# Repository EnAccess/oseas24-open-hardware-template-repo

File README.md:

<p align="center">
  
</p>
<p align="center">
    9-10 May | Open Source in Energy Access Symposium Hackathon
</p>

---

## Open Hardware Template Repository

**Stack:** KiCAD, Python scripting

**Helpful experiences:** KiCAD automation, CI/CD pipelines

**Abstract:** The tooling for Open Hardware repositories is currently undergoing rapid development. It can be overwhelming for an electrical engineer working on the PCB’s to follow up on all this.

## Challenge

The goal of this workgroup is to create a KiCAD template repository with the some of following features (in no particular order)

- Automatic diff generation for PCB’s and Schematics
- KiCanvas WebViewer Link integration
- CI pipeline to run lint checks: DRC rules check, conventions, etc..
- Release management, using GitHub tags
- Workflow to update the release tag as labels on the PCB
- Deploy workflow that generates production files and makes them available in the release (not part of version control)
- Auto-generated documentation (incl. versioning)
- Deployment of documentation (keeping docs of older PCB revisions)

This repo uses a sample KiCAD PCB from the [Cicada Project](https://github.com/EnAccess/Cicada-GSM-HW).

As part of the Open BMS we have already explored some features of the amazing KiBot tool. Also, the recent release of KiCAD v8 enriches the native KiCAD CLI with some features

**Expected outcome:** The optimal outcome of this challenge would be a repository template including all above mentioned features and integrations. However we know time is short and anything getting us closer to this can be a great success (e.g. an early draft repo + a detailed specifications and to-do list).

## Getting Started

- Join the OSEAS24 Discord server: https://community.oseas.org/
- Introduce yourself in #introductions channel and join this topic’s channel
- Confirm you have access to the following Repos
  - https://github.com/EnAccess/oseas24-open-hardware-template-repo
- For physical participants: Bring a computer (and required Adapters) for some hacking 🤖🧑‍💻
- Read through the information and resources section

Contact person(s): Daniel (remote) / Martin (remote)

## Further information and resources

- https://github.com/LibreSolar/bms-c1/pull/48
- https://www.kicad.org/blog/2024/02/Version-8.0.0-Released/
- https://github.com/INTI-CMNB/KiBot
- KiCanvas: KiCad web viewer
  - Link: https://kicanvas.org/
  - Example: https://kicanvas.org/?github=https%3A%2F%2Fgithub.com%2FLibreSolar%2Fbms-c1%2Ftree%2Fmain%2Fkicad
- Interactive HTML BoM
  - https://github.com/openscopeproject/InteractiveHtmlBom
- Other example of nice project: https://github.com/OpenCleanEnergy/OpenMI

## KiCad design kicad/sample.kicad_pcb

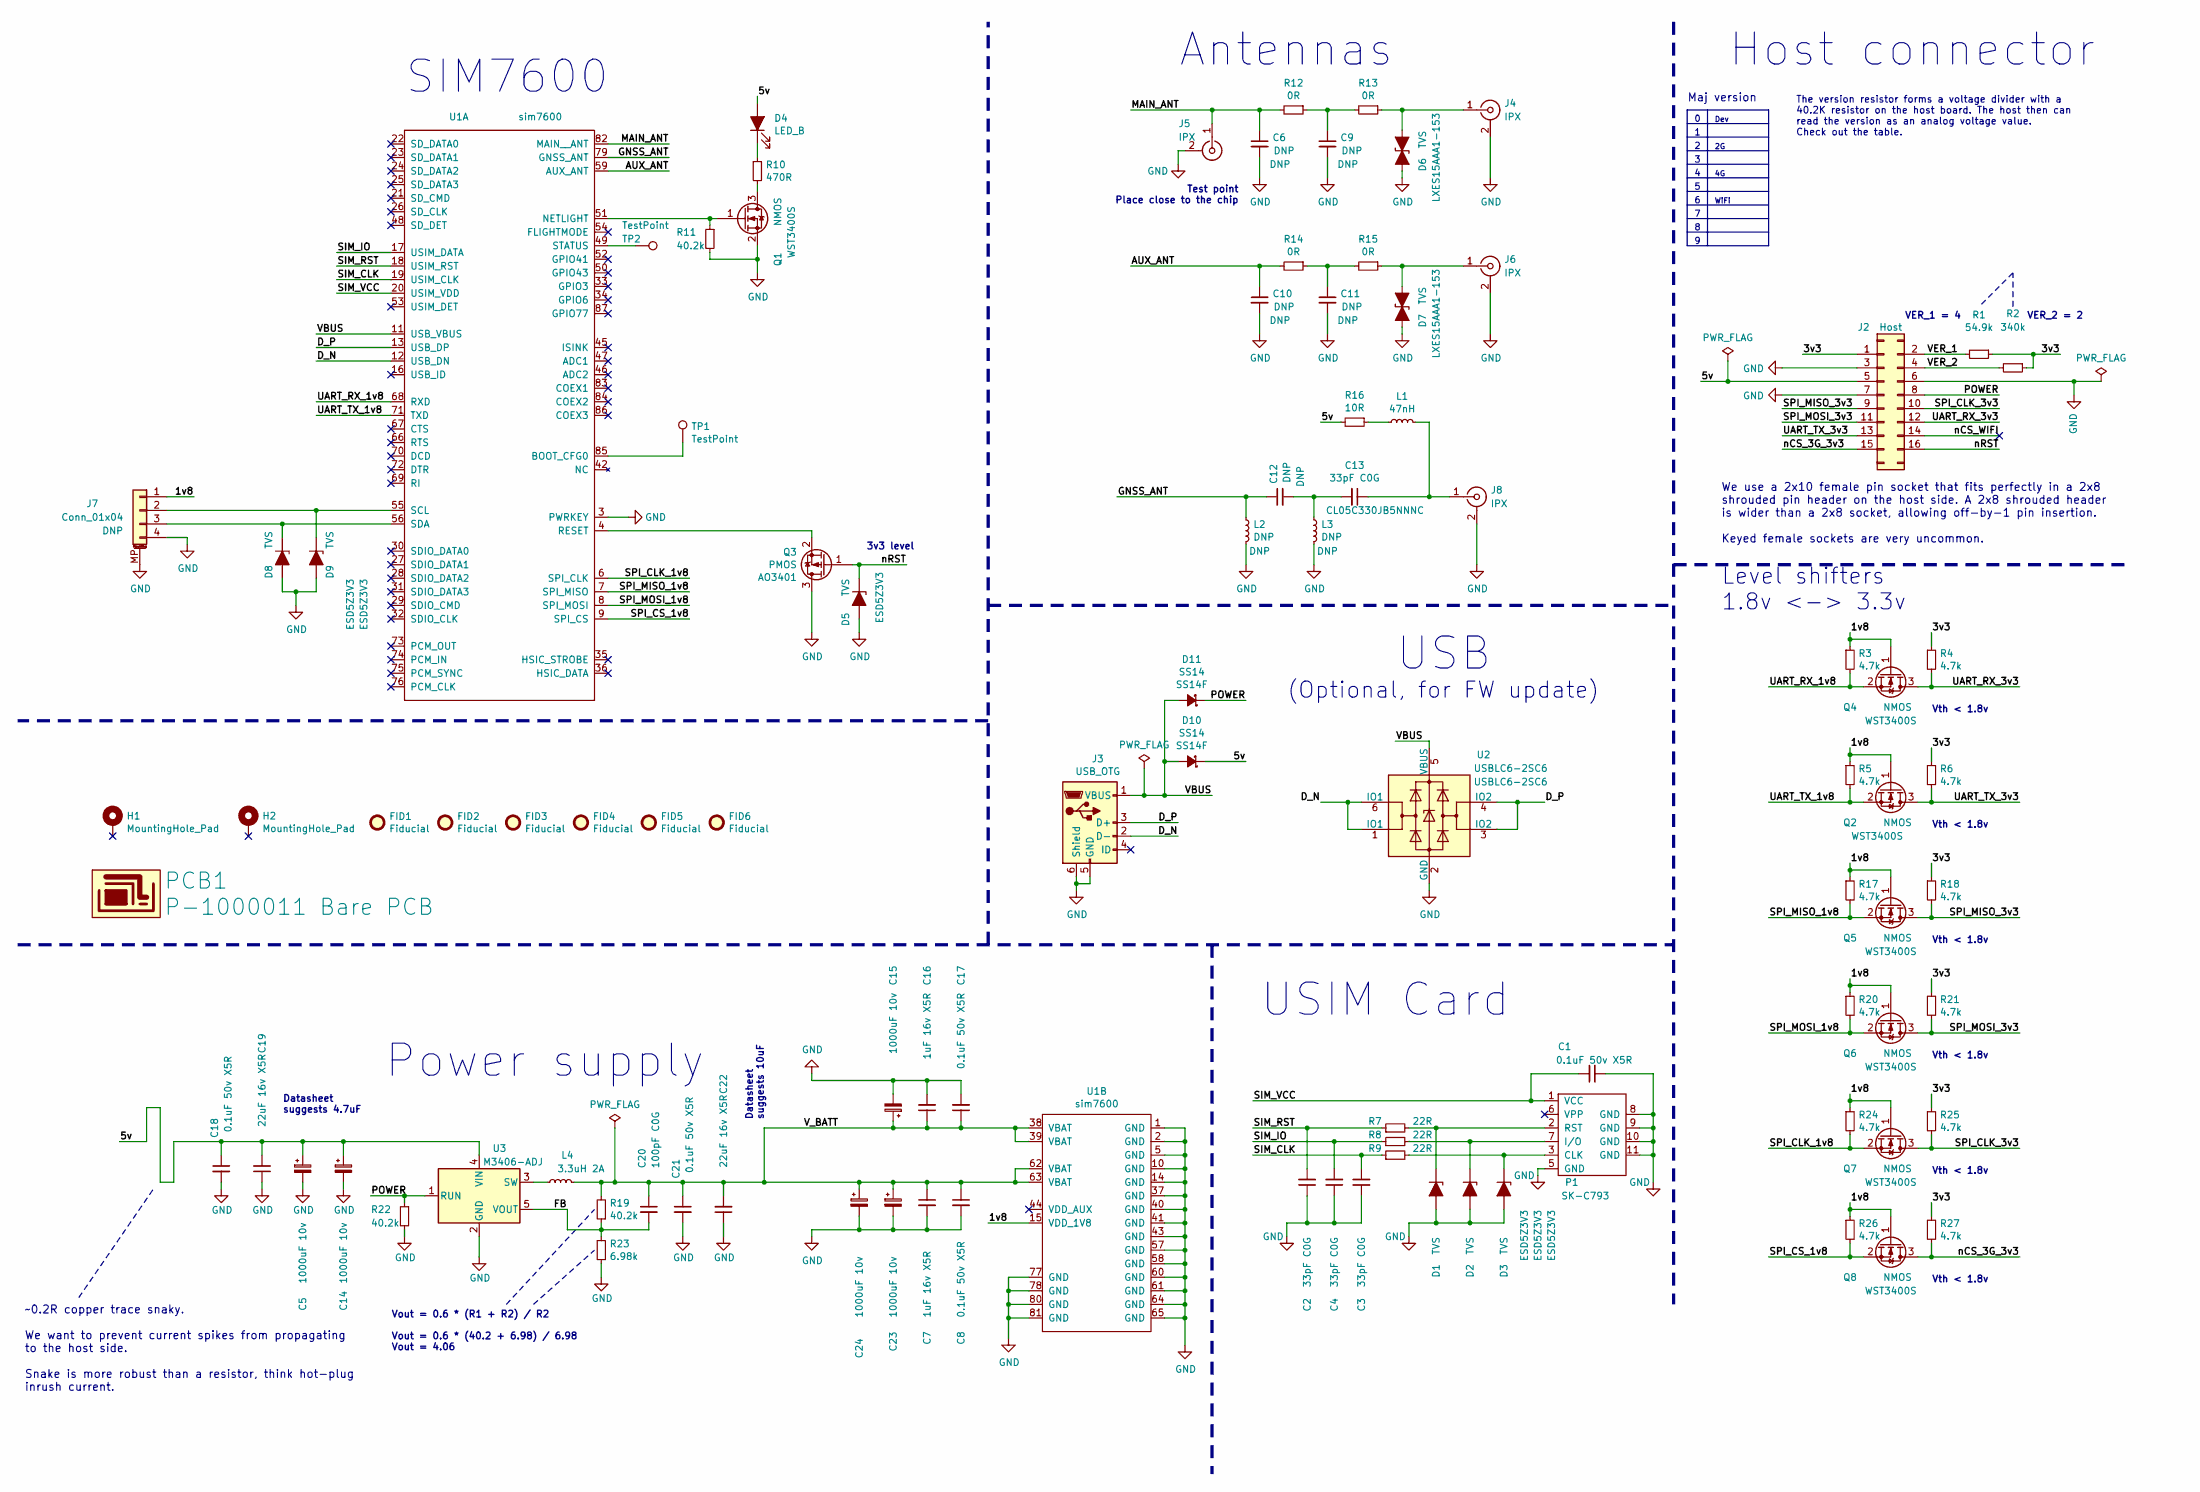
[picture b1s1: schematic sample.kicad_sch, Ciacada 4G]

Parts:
C1, C8, C17, C18, C21: 0.1uF 50v X5R; C_0603_1608Metric; MPN CL10B104KB8NNNC
C2, C3, C4, C13: 33pF C0G; C_0402_1005Metric; MPN CL05C330JB5NNNC
C5, C14, C15, C23, C24: 1000uF 10v; CP_Radial_D8.0mm_P3.50mm; MPN C3299
C6, C9, C10, C11, C12: DNP; C_0402_1005Metric
C7, C16: 1uF 16v X5R; C_0603_1608Metric; MPN CL10A105KB8NNNC
C19, C22: 22uF 16v X5R; C_0805_2012Metric; MPN CL21A226MOQNNNE
C20: 100pF C0G; C_0402_1005Metric; MPN CL05C101JB5NNNC
D1, D2, D3, D5, D8, D9: TVS; D_SOD-523; MPN ESD5Z3V3
D4: LED_B; D_0603_1608Metric; MPN BL-HB336G-TRB
D6, D7: TVS; D_0402_1005Metric; MPN LXES15AAA1-153
D10, D11: SS14; D_SMA; MPN SS14F
FID1, FID2, FID3, FID4, FID5, FID6: Fiducial; Fiducial_1mm_Mask2mm
H1, H2: MountingHole_Pad; MountingHole_3.2mm_M3_ISO14580_Pad
J2: Host; PinSocket_2x08_P2.54mm_Vertical_padded; MPN C30867
J3: USB_OTG; ZX62D-B-5PA8; MPN C10418
J4, J5, J6, J8: IPX; U.FL_Molex_MCRF_73412-0110_Vertical; MPN U.FL-R-SMT-1(80)
J7: Conn_01x04; JST_PH_S4B-PH-SM4-TB_1x04-1MP_P2.00mm_Horizontal
L1: 47nH; L_0402_1005Metric; MPN SDCL1005C47NJTDF
L2, L3: DNP; L_0402_1005Metric
L4: 3.3uH 2A; L_4030_Handsoldering; MPN FPI0403F-3R3M
P1: SK-C793; MPN SK-C793
PCB1: P-1000011 Bare PCB
Q1, Q2, Q4, Q5, Q6, Q7, Q8: NMOS; SOT-23; MPN WST3400S
Q3: PMOS; SOT-23; MPN AO3401
R1: 54.9k; R_0402_1005Metric; MPN 0402WGF5492TCE
R2: 340k; R_0402_1005Metric; MPN 0402WGF3403TCE
R3, R4, R5, R6, R17, R18, R20, R21, R24, R25, R26, R27: 4.7k; R_0402_1005Metric; MPN 0402WGF4701TCE
R7, R8, R9: 22R; R_0402_1005Metric; MPN 0402WGF220JTCE
R10: 470R; R_0402_1005Metric; MPN 0402WGF4700TCE
R11, R19, R22: 40.2k; R_0402_1005Metric; MPN 0402WGF4022TCE
R12, R13, R14, R15: 0R; R_0402_1005Metric; MPN 0402WGF0000TCE
R16: 10R; R_0402_1005Metric; MPN 0402WGF100JTCE
R23: 6.98k; R_0402_1005Metric; MPN 0402WGF6981TCE
TP1, TP2: TestPoint; TestPoint_Pad_D1.5mm
U1: sim7600; MPN SIM7600CE-L1C
U2: USBLC6-2SC6; SOT-23-6; MPN USBLC6-2SC6
U3: M3406-ADJ; TSOT-23-5; MPN M3406-ADJ

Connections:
/1v8: J7.1, Q2.1 (G), Q4.1 (G), Q5.1 (G), Q6.1 (G), Q7.1 (G), Q8.1 (G), R3.1, R5.1, R17.1, R20.1, R24.1, R26.1, U1.15 (VDD_1V8)
/3v3: J2.1, R1.1, R2.1, R4.1, R6.1, R18.1, R21.1, R25.1, R27.1
/5v: C5.1, C14.1, C18.1, C19.2, D4.2 (A), D10.1 (K), J2.5, R16.2, U3.4 (VIN)
/AUX_ANT: C10.1, R14.2, U1.59 (AUX_ANT)
/D_N: J3.2 (D-), U1.12 (USB_DN), U2.1 (IO1), U2.6 (IO1)
/D_P: J3.3 (D+), U1.13 (USB_DP), U2.3 (IO2), U2.4 (IO2)
/FB: C20.2, R19.1, R23.2, U3.5 (VOUT)
/GNSS_ANT: C12.1, L2.1, U1.79 (GNSS_ANT)
/MAIN_ANT: C6.1, J5.1 (In), R12.2, U1.82 (MAIN__ANT)
/POWER: D11.1 (K), J2.8, R22.1, U3.1 (RUN)
/SIM_CLK: C3.2, R9.1, U1.19 (USIM_CLK)
/SIM_IO: C4.2, R8.1, U1.17 (USIM_DATA)
/SIM_RST: C2.2, R7.1, U1.18 (USIM_RST)
/SIM_VCC: C1.1, P1.1 (VCC), U1.20 (USIM_VDD)
/SPI_CLK_1v8: Q7.2 (S), R24.2, U1.6 (SPI_CLK)
/SPI_CLK_3v3: J2.10, Q7.3 (D), R25.2
/SPI_CS_1v8: Q8.2 (S), R26.2, U1.9 (SPI_CS)
/SPI_MISO_1v8: Q5.2 (S), R17.2, U1.7 (SPI_MISO)
/SPI_MISO_3v3: J2.9, Q5.3 (D), R18.2
/SPI_MOSI_1v8: Q6.2 (S), R20.2, U1.8 (SPI_MOSI)
/SPI_MOSI_3v3: J2.11, Q6.3 (D), R21.2
/UART_RX_1v8: Q4.2 (S), R3.2, U1.68 (RXD)
/UART_RX_3v3: J2.12, Q4.3 (D), R4.2
/UART_TX_1v8: Q2.2 (S), R5.2, U1.71 (TXD)
/UART_TX_3v3: J2.13, Q2.3 (D), R6.2
/VBUS: D10.2 (A), D11.2 (A), J3.1 (VBUS), U1.11 (USB_VBUS), U2.5 (VBUS)
/VER_1: J2.2, R1.2
/VER_2: J2.4, R2.2
/V_BATT: C7.1, C8.1, C15.1, C16.1, C17.1, C20.1, C21.1, C22.2, C23.1, C24.1, L4.2, R19.2, U1.38 (VBAT), U1.39 (VBAT), U1.62 (VBAT), U1.63 (VBAT)
/nCS_3G_3v3: J2.15, Q8.3 (D), R27.2
/nCS_WIFI: J2.14
/nRST: D5.1 (K), J2.16, Q3.1 (G)
GND: C1.2, C2.1, C3.1, C4.1, C5.2, C6.2, C7.2, C8.2, C9.2, C10.2, C11.2, C14.2, C15.2, C16.2, C17.2, C18.2, C19.1, C21.2, C22.1, C23.2, C24.2, D1.2 (A), D2.2 (A), D3.2 (A), D5.2 (A), D6.2 (A2), D7.2 (A2), D8.2 (A), D9.2 (A), J2.3, J2.6, J2.7, J3.5 (GND), J3.6 (Shield), J4.2 (Ext), J5.2 (Ext), J6.2 (Ext), J7.4, J7.MP (MountPin), J8.2 (Ext), L2.2, L3.2, P1.5 (GND), P1.8 (GND), P1.9 (GND), P1.10 (GND), P1.11 (GND), Q1.2 (S), Q3.3 (D), R11.2, R22.2, R23.1, U1.1 (GND), U1.2 (GND), U1.3 (PWRKEY), U1.5 (GND), U1.10 (GND), U1.14 (GND), U1.37 (GND), U1.40 (GND), U1.41 (GND), U1.43 (GND), U1.57 (GND), U1.58 (GND), U1.60 (GND), U1.61 (GND), U1.64 (GND), U1.65 (GND), U1.77 (GND), U1.78 (GND), U1.80 (GND), U1.81 (GND), U2.2 (GND), U3.2 (GND)
unnamed: C9.1, R12.1, R13.2
unnamed: C11.1, R14.1, R15.2
unnamed: C12.2, C13.2, L3.1
unnamed: C13.1, J8.1 (In), L1.2
unnamed: D1.1 (K), P1.2 (RST), R7.2
unnamed: D2.1 (K), P1.7 (I/O), R8.2
unnamed: D3.1 (K), P1.3 (CLK), R9.2
unnamed: D4.1 (K), R10.1
unnamed: D6.1 (A1), J4.1 (In), R13.1
unnamed: D7.1 (A1), J6.1 (In), R15.1
unnamed: D8.1 (K), J7.3, U1.56 (SDA)
unnamed: D9.1 (K), J7.2, U1.55 (SCL)
unnamed: L1.1, R16.1
unnamed: L4.1, U3.3 (SW)
unnamed: Q1.1 (G), R11.1, U1.51 (NETLIGHT)
unnamed: Q1.3 (D), R10.2
unnamed: Q3.2 (S), U1.4 (RESET)
unnamed: TP1.1, U1.85 (BOOT_CFG0)
unnamed: TP2.1, U1.49 (STATUS)

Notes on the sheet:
~0.2R copper trace snaky. We want to prevent current spikes from propagating to the host side. Snake is more robust than a resistor, think hot-plug inrush current.
Dev
Vth < 1.8v
USB
Level shifters 1.8v <-> 3.3v
USIM Card
The version resistor forms a voltage divider with a 40.2K resistor on the host board. The host then can read the version as an analog voltage value. Check out the table.
(Optional, for FW update)
Test point Place close to the chip
Vout = 0.6 * (R1 + R2) / R2 Vout = 0.6 * (40.2 + 6.98) / 6.98 Vout = 4.06
Datasheet suggests 4.7uF
VER_1 = 4
Maj version
Power supply
Antennas
Datasheet suggests 10uF
WiFi
We use a 2x10 female pin socket that fits perfectly in a 2x8 shrouded pin header on the host side. A 2x8 shrouded header is wider than a 2x8 socket, allowing off-by-1 pin insertion. Keyed female sockets are very uncommon.
3v3 level
SIM7600
Host connector
VER_2 = 2

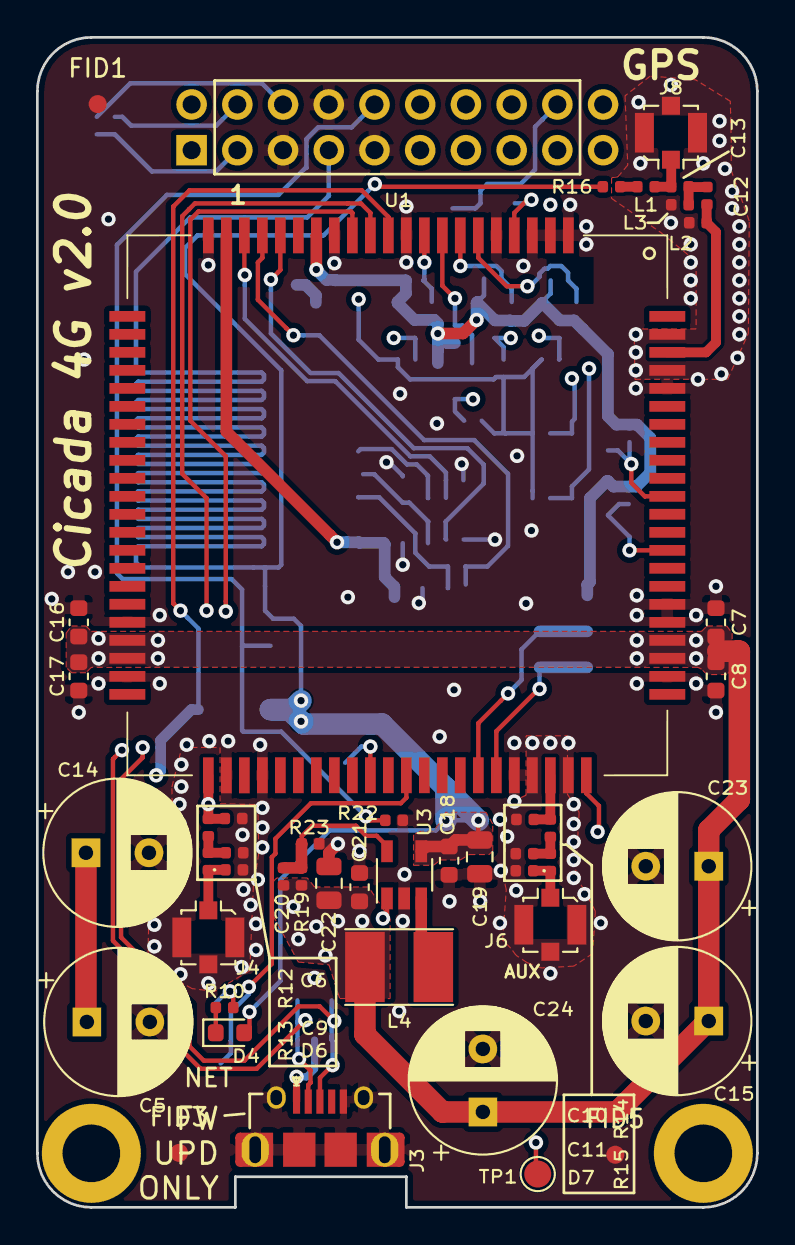
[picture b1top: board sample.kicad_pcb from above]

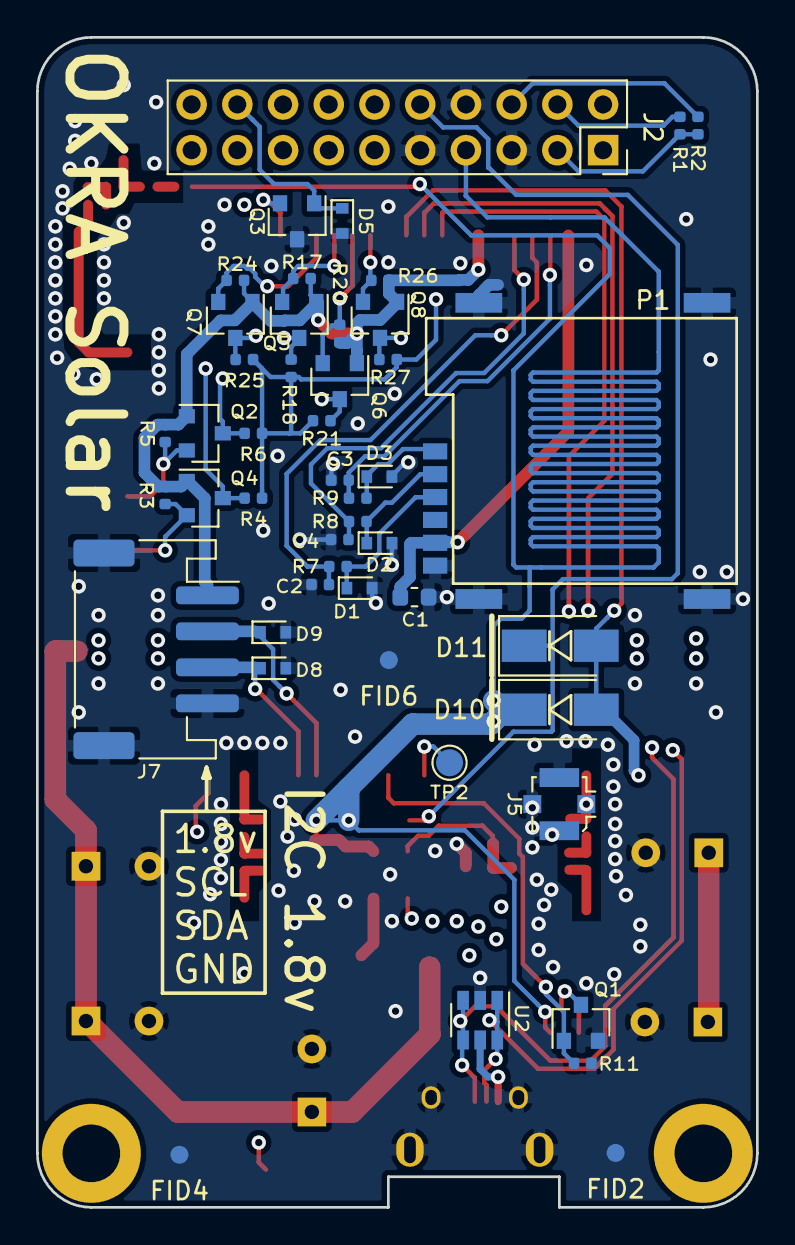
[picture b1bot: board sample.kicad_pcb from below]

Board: 4 copper layers, 40.0 x 65.0 mm, 95 parts (47 on the bottom side), 51 nets.

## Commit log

2024-05-02 Create LICENSE
2024-05-08 Add sample and more instructions
2024-09-19 Add `CODE_OF_CONDUCT.md`
2024-09-23 Add `.github/SECURITY.md`
2024-09-23 Add `.github/PULL_REQUEST_TEMPLATE.md`
2024-09-23 Add `.github/ISSUE_TEMPLATE/config.yml`
2024-09-23 Add `.github/ISSUE_TEMPLATE/feature_request.yml`
2024-09-23 Add `.github/ISSUE_TEMPLATE/bug_report.yml`
2024-09-23 Add `CONTRIBUTING.md`
2025-04-28 Add `DISCORD_ETIQUETTE.md`
